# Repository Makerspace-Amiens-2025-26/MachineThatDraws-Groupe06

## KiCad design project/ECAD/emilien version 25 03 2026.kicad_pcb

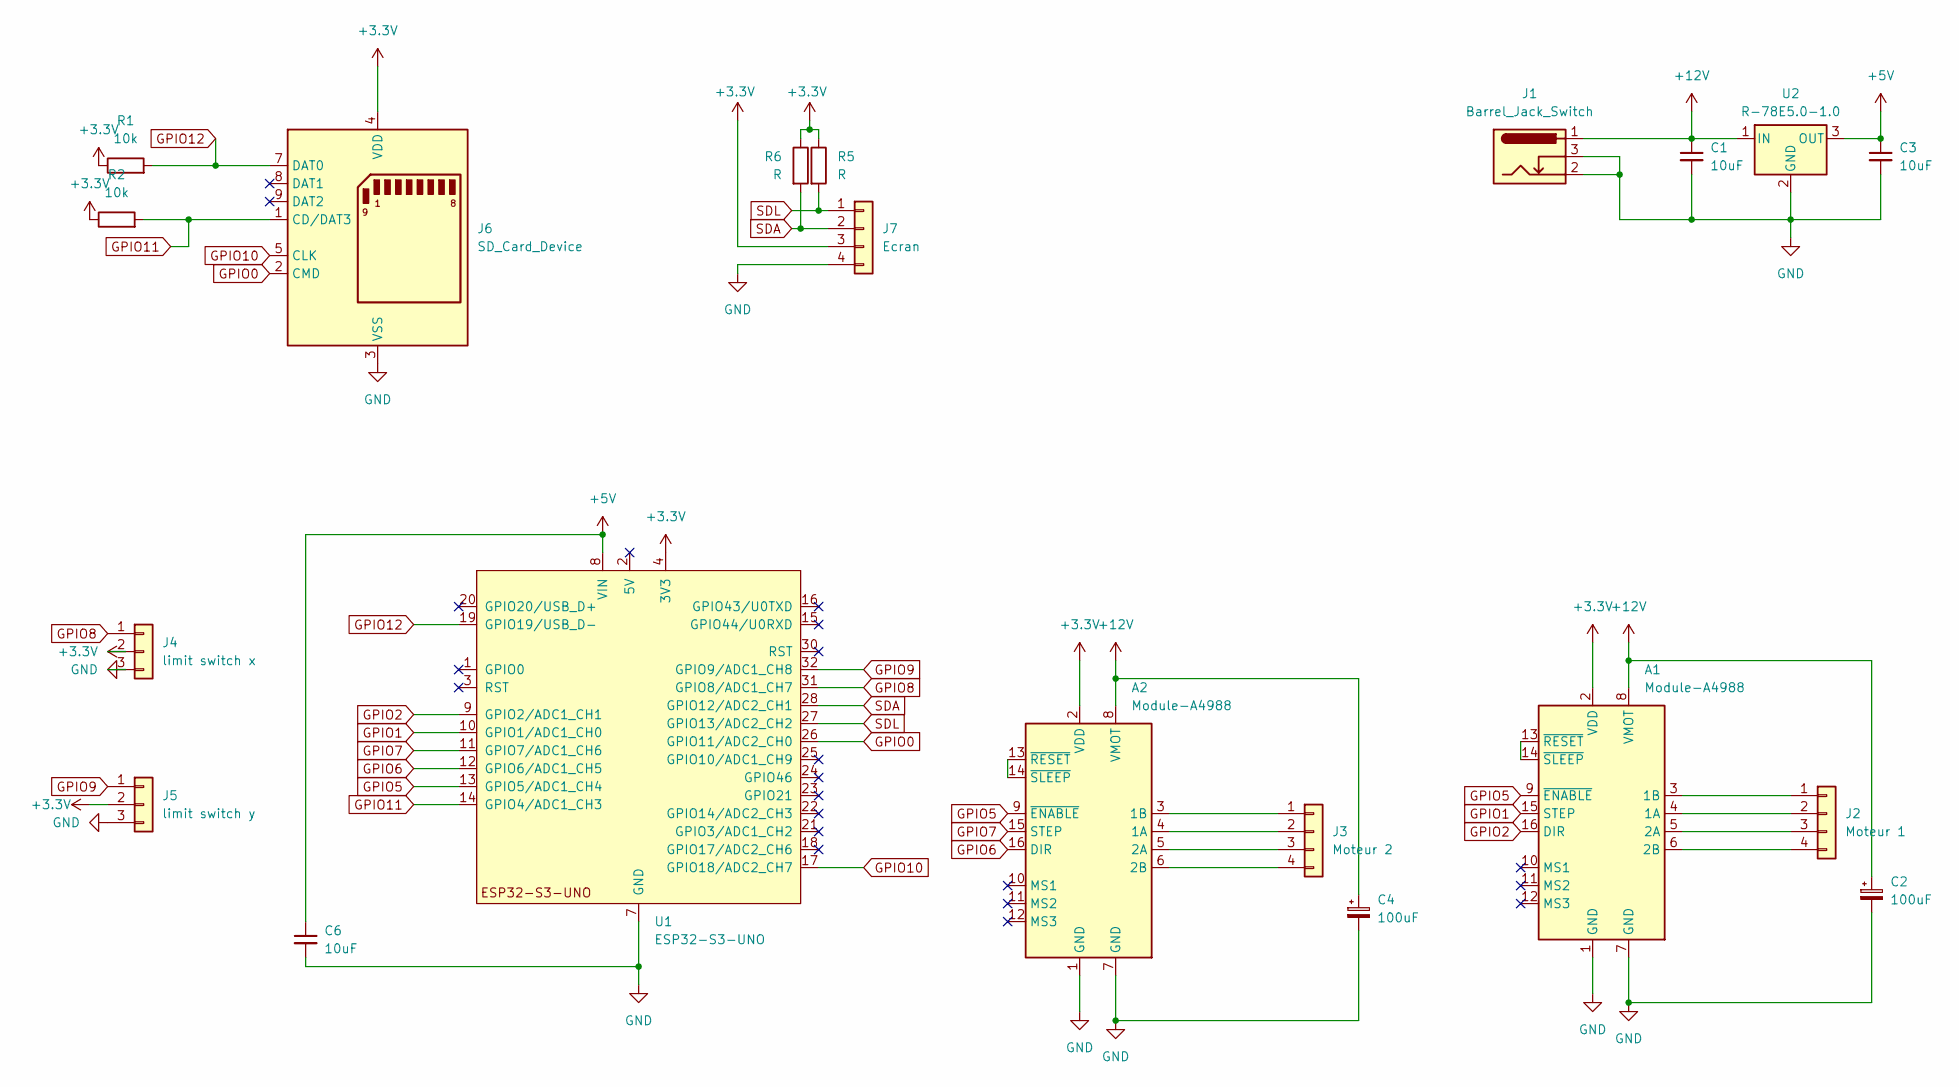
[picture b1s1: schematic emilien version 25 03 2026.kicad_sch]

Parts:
A1, A2: Module-A4988; Pololu_Breakout-16_15.2x20.3mm
C1, C3, C6: 10uF; C_1206_3216Metric
C2, C4: 100uF; CP_Radial_D8.0mm_P3.50mm
J1: Barrel_Jack_Switch; BarrelJack_Horizontal
J2: Moteur 1; PinHeader_1x04_P2.54mm_Vertical
J3: Moteur 2; PinHeader_1x04_P2.54mm_Vertical
J4: limit switch x; PinHeader_1x03_P2.54mm_Vertical
J5: limit switch y; PinHeader_1x03_P2.54mm_Vertical
J6: SD_Card_Device; SD_Hirose_DM1AA_SF_PEJ82
J7: Ecran; PinHeader_1x04_P2.54mm_Vertical
R1, R2: 10k; R_Axial_DIN0207_L6.3mm_D2.5mm_P7.62mm_Horizontal
R5, R6: R; R_Axial_DIN0207_L6.3mm_D2.5mm_P7.62mm_Horizontal
U1: ESP32-S3-UNO; ESP_S3_UNO
U2: R-78E5.0-1.0; Converter_DCDC_RECOM_R-78E-0.5_THT

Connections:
+3.3V: A1.2 (VDD), A2.2 (VDD), J4.2, J5.2, J6.4 (VDD), J7.3, R1.1, R2.1, R5.1, R6.1, U1.4 (3V3)
GND: A1.1 (GND), A1.7 (GND), A2.1 (GND), A2.7 (GND), C1.2, C2.2, C3.2, C4.2, C6.2, J1.2, J1.3, J4.3, J5.3, J6.3 (VSS), J6.6 (VSS), J7.4, U1.6 (GND), U1.7 (GND), U1.29 (GND), U2.2 (GND)
GPIO0: J6.2 (CMD), U1.26 (GPIO11/ADC2_CH0)
GPIO1: A1.15 (STEP), U1.10 (GPIO1/ADC1_CH0)
GPIO2: A1.16 (DIR), U1.9 (GPIO2/ADC1_CH1)
GPIO5: A1.9 (~ENABLE), A2.9 (~ENABLE), U1.13 (GPIO5/ADC1_CH4)
GPIO6: A2.16 (DIR), U1.12 (GPIO6/ADC1_CH5)
GPIO7: A2.15 (STEP), U1.11 (GPIO7/ADC1_CH6)
GPIO8: J4.1, U1.31 (GPIO8/ADC1_CH7)
GPIO9: J5.1, U1.32 (GPIO9/ADC1_CH8)
GPIO10: J6.5 (CLK), U1.17 (GPIO18/ADC2_CH7)
GPIO11: J6.1 (CD/DAT3), R2.2, U1.14 (GPIO4/ADC1_CH3)
GPIO12: J6.7 (DAT0), R1.2, U1.19 (GPIO19/USB_D-)
unnamed: A1.4 (1A), J2.2
unnamed: A1.3 (1B), J2.1
unnamed: A1.5 (2A), J2.3
unnamed: A1.6 (2B), J2.4
unnamed: A1.13 (~RESET), A1.14 (~SLEEP)
unnamed: A2.4 (1A), J3.2
unnamed: A2.3 (1B), J3.1
unnamed: A2.5 (2A), J3.3
unnamed: A2.6 (2B), J3.4
unnamed: A2.13 (~RESET), A2.14 (~SLEEP)
SDA: J7.2, R6.2, U1.28 (GPIO12/ADC2_CH1)
SDL: J7.1, R5.2, U1.27 (GPIO13/ADC2_CH2)

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
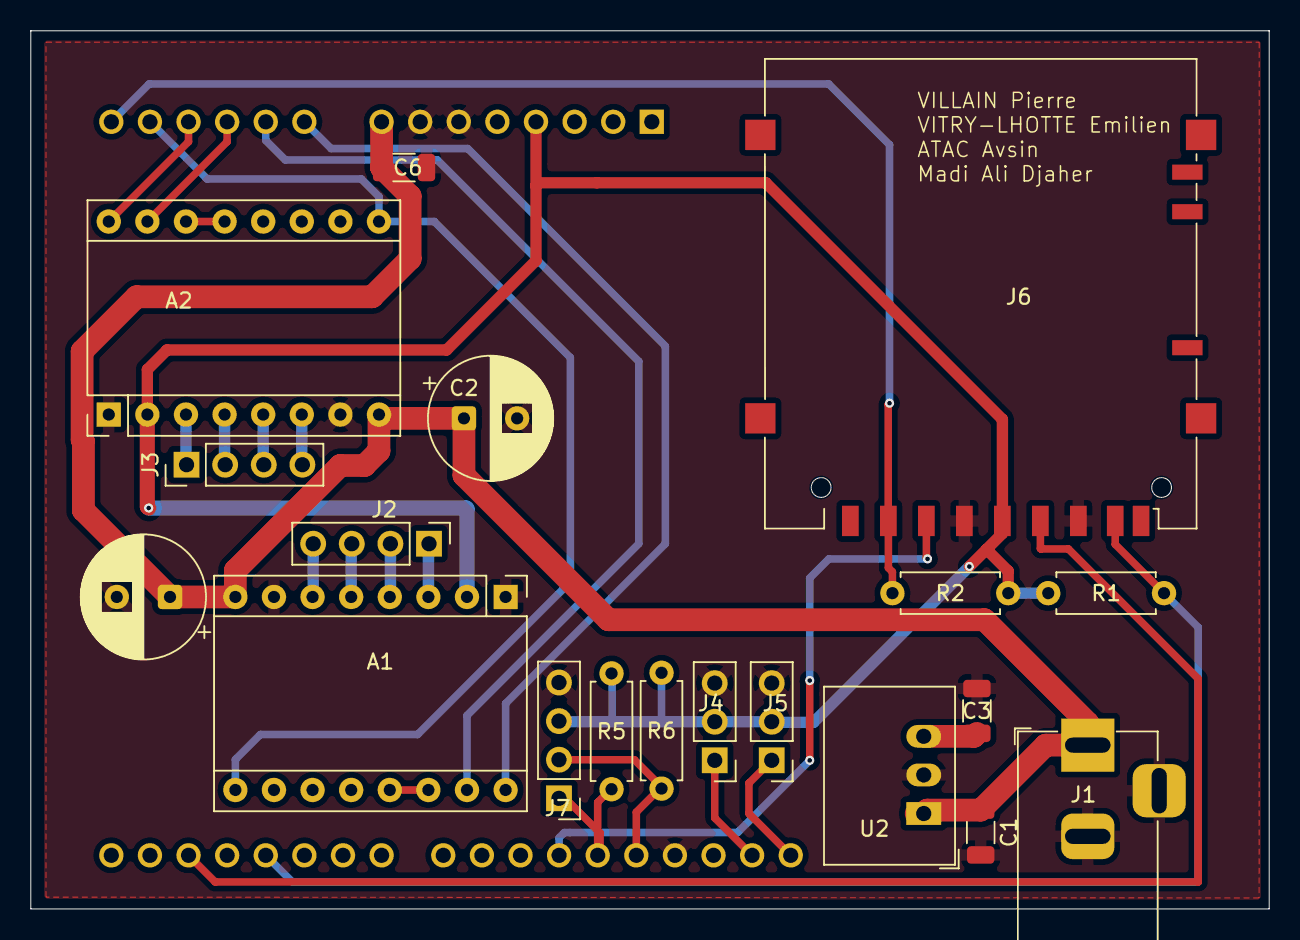
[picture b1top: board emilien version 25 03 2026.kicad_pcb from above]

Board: 2 copper layers, 81.5 x 57.8 mm, 20 parts (0 on the bottom side), 27 nets.

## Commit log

2026-03-11 Added PCB sources
2026-03-20 Kikad V2 modification d'alban effectué
2026-04-03 Fix theming - Clean revert
2026-04-03 mise a jour du site
2026-04-22 mise à jour du site
2026-04-22 mise a jour
2026-04-24 PCB upload
2026-04-25 Upload new ECAD
2026-04-27 ECAD final version
2026-04-27 enieme version du ecad pour alban
    bisous bisous
2026-04-27 fix some wiring problems
2026-05-12 maj2
2026-05-12 maj3
2026-05-12 sitemodifief
2026-05-12 Remove accidental empty etudes.md
2026-05-12 Fix nav_sort invalid value in _config.yml
2026-05-12 Fix CI: replace github-pages gem with jekyll 4, commit Gemfile.lock
2026-05-12 Add x86_64-linux platform to Gemfile.lock for GitHub Actions
2026-05-17 Rebuild site: parent/child nav structure, fix CI Gemfile
2026-05-17 Add --trace to Jekyll build for error visibility, bump cache-version
2026-05-17 Print Jekyll error to step summary for debugging
2026-05-17 Fix CI: use Jekyll 4 + no bundler cache to fix Dart Sass compatibility
2026-05-17 site github
2026-05-17 Fix CI: commit Gemfile.lock with linux platform to ensure reproducible builds
2026-05-17 Fix sidebar truncation and full-width layout
2026-05-17 Redesign: split hero with OnShape 3D embed, fix sidebar layout
2026-05-17 Simplify homepage: plain hero, 3D model below
2026-05-17 Homepage: dark hero section, 3 buttons incl. OnShape, remove sidebar logo
2026-05-17 Remove stats grid from homepage
2026-05-17 Remove duplicate text and repeated pipeline across pages
2026-05-17 Enrich all pages with detailed placeholder structure for content fill-in
2026-05-22 modif
2026-05-22 changement des partie
2026-06-01 updt website
2026-06-01 html website
2026-06-01 update CI
2026-06-01 Ci update
2026-06-01 fix: remove .history submodule, add to gitignore
2026-06-01 upload sites
2026-06-01 trigger deploy
2026-06-01 update, web
2026-06-01 upload website
2026-06-01 update website
2026-06-01 update index
2026-06-01 sites web navbar
2026-06-01 home
2026-06-01 project update
2026-06-01 upload animation
2026-06-01 scroll
2026-06-02 tests
2026-06-02 Mise à jour 3D et CSS
2026-06-02 tess
2026-06-02 tetss
2026-06-02 3d modele
2026-06-03 presentation
2026-06-03 udate
2026-06-03 fnis
2026-06-04 Ajout photo machine dans présentation générale
2026-06-04 Réduction taille photo machine
2026-06-04 Simplification fiche technique présentation
2026-06-04 Ajout cahier des charges dans objectifs du projet
2026-06-04 Refonte page objectifs : ajout objectif principal, simplification contraintes
2026-06-04 Remplacement tableaux par texte dans objectifs
2026-06-05 Suppression icônes cartes accueil
2026-06-05 Remplacement tableaux par texte dans étude technique
2026-06-05 Simplification étude technique : suppression gras, coûts, infos trop précises
2026-06-05 Ajout photos moteur NEMA 17 et servomoteur dans motorisation
2026-06-05 Suppression régulateur R-78E5 dans électronique
2026-06-05 Remise des composants 3D dans structure générale
2026-06-05 Amélioration layout composants 3D structure générale
2026-06-05 Simplification page impression 3D
2026-06-05 Suppression mention BambuLab
2026-06-05 Suppression section photos pièces impression 3D
2026-06-05 Simplification composants mécaniques : texte, quantités correctes, suppression bagues
2026-06-05 Suppression étape 8 mécanique
2026-06-05 Suppression placeholders difficultés et photos mécanique
2026-06-05 Simplification page électronique câblage
2026-06-05 Simplification tests mise au point + ajout vidéo YouTube
2026-06-05 Restructuration complète de la navigation : 8 pages thématiques
2026-06-05 images du pcb et schéma elec
2026-06-05 derniere modif
2026-06-06 ajout / correction
2026-06-06 porte stylo
2026-06-08 Add poster
